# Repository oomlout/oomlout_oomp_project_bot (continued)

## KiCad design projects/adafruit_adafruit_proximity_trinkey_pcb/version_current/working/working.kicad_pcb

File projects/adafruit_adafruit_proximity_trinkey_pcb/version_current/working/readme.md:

# OOMP Project  
## Adafruit-Proximity-Trinkey-PCB  by adafruit  
  
oomp key: oomp_projects_flat_adafruit_adafruit_proximity_trinkey_pcb  
(snippet of original readme)  
  
-- Adafruit Proximity Trinkey PCB  
  
<a href="http://www.adafruit.com/products/5022"><br/>  
Click here to purchase one from the Adafruit shop</a>  
  
PCB files for the Adafruit Proximity Trinkey.   
  
Format is EagleCAD schematic and board layout  
* https://www.adafruit.com/product/5022  
  
--- Description  
  
It's half USB Key, half Adafruit Trinket M0, half APDS9960 breakout...it's Proximity Trinkey, the circuit board with a Trinket M0 heart, APDS9960 Proximity, Light, RGB, and Gesture Sensor, and two RGB NeoPixels for a customizable glow. We wanted to make it super-easy to add one of our most popular combination-sensors to any computer with a USB port and this one is ready to go in an instant.  
  
The PCB is designed to slip into any USB A port on a computer or laptop. There's an ATSAMD21 microcontroller on board with just enough circuitry to keep it happy. One pin of the microcontroller connects to the two NeoPixel LEDs. Two other pins are used as capacitive touch inputs on the end - if you look carefully you can see the slotted end has left and right touch pads. A reset button lets you enter bootloader mode if necessary. That's it!  
  
The SAMD21 can run CircuitPython or Arduino very nicely - both have existing APDS9960, NeoPixel and our FreeTouch (capacitive touch) libraries. Over the USB connection, you can have serial, MIDI, or HID connectivity. The Proximity Trinkey is perfect for simple projects that want to use motion, light or color sen  
  full source readme at [readme_src.md](readme_src.md)  
  
source repo at: [https://github.com/adafruit/Adafruit-Proximity-Trinkey-PCB](https://github.com/adafruit/Adafruit-Proximity-Trinkey-PCB)  
## Board  

## Schematic  

[schematic pdf](working_schematic.pdf)  
## Images

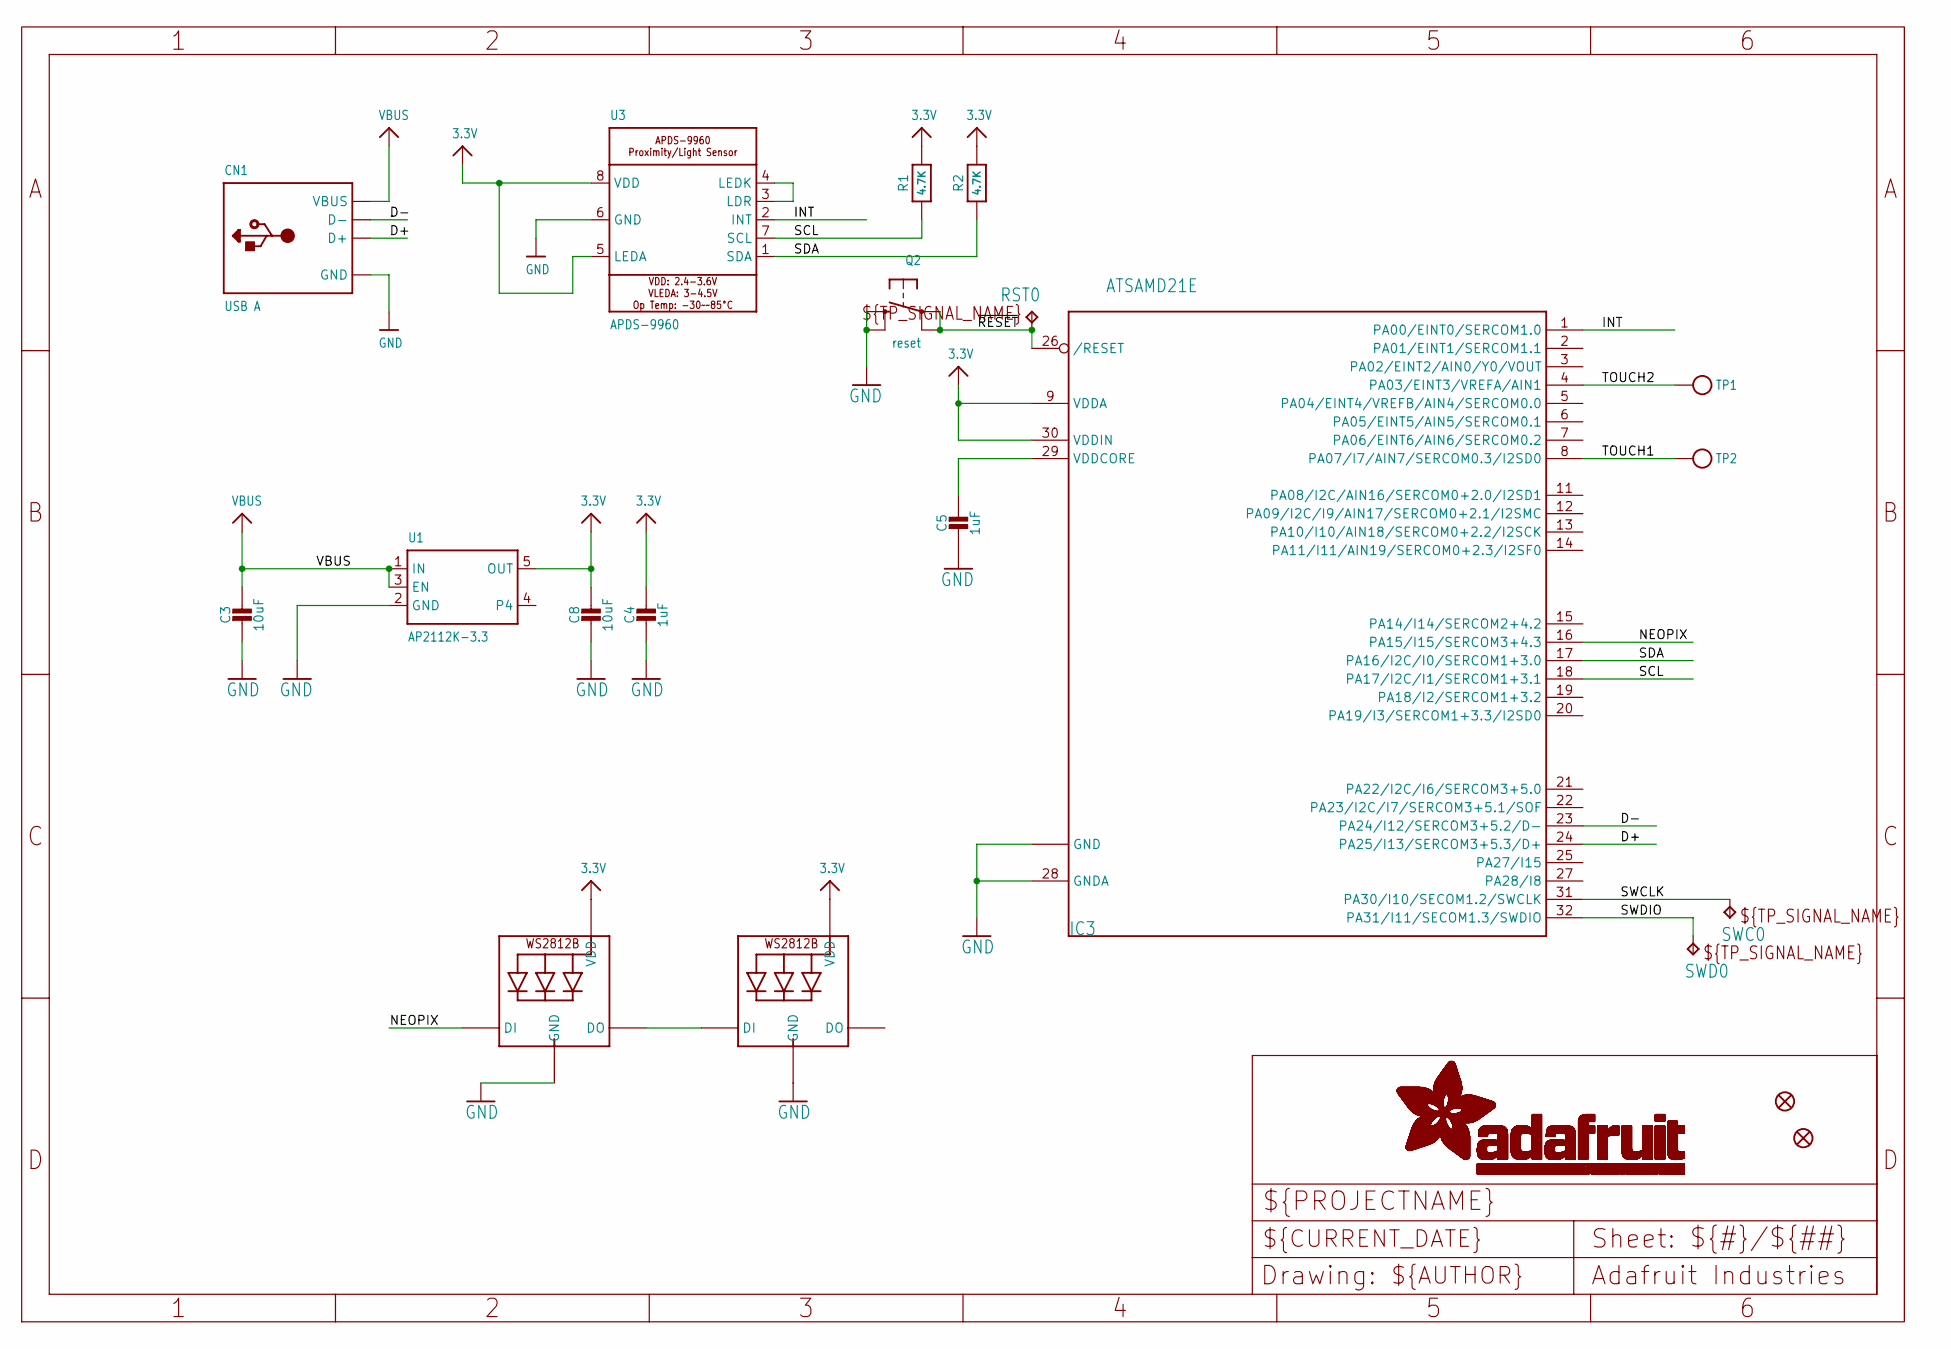
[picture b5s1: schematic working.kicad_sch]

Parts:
C3, C8: 10uF; 0805-NO
C4, C5: 1uF; 0603-NO
CN1: USB A; USBA_PCB
FID1, FID2: FIDUCIAL_1MM
IC3: ATSAMD21E; QFN32_5MM
LED1, LED2: WS2812B3535; LED3535
Q2: reset; BTN_KMR2_4.6X2.8
R1, R2: 4.7K; 0603-NO
RST0: TPTP16R; TP16R
SWC0: TPTP15R; TP15R
SWD0: TPTP16R; TP16R
TP1, TP2: TESTPOINTROUND1.5MMNO; TESTPOINT_ROUND_1.5MM_NO
U1: AP2112K-3.3; SOT23-5
U3: APDS-9960

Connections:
3.3V: C4.1, C8.1, IC3.9 (VDDA), IC3.30 (VDDIN), LED1.2 (VDD), LED2.2 (VDD), R1.2, R2.2, U1.5 (OUT), U3.5 (LEDA), U3.8 (VDD)
D+: CN1.USB_PLUS (D+), IC3.24 (PA25/I13/SERCOM3+5.3/D+)
D-: CN1.USB_NEG (D-), IC3.23 (PA24/I12/SERCOM3+5.2/D-)
GND: C3.2, C4.2, C5.2, C8.2, CN1.GND, IC3.10 (GND), IC3.28 (GNDA), IC3.33 (GND), LED1.4 (GND), LED2.4 (GND), Q2.B (S), Q2.B' (S1), U1.2 (GND), U3.6 (GND)
INT: IC3.1 (PA00/EINT0/SERCOM1.0), U3.2 (INT)
unnamed: LED1.1 (DI), LED2.3 (DO)
unnamed: U3.3 (LDR), U3.4 (LEDK)
NEOPIX: IC3.16 (PA15/I15/SERCOM3+4.3), LED2.1 (DI)
SCL: IC3.18 (PA17/I2C/I1/SERCOM1+3.1), R1.1, U3.7 (SCL)
SDA: IC3.17 (PA16/I2C/I0/SERCOM1+3.0), R2.1, U3.1 (SDA)
SWCLK: IC3.31 (PA30/I10/SECOM1.2/SWCLK), SWC0.TP
SWDIO: IC3.32 (PA31/I11/SECOM1.3/SWDIO), SWD0.TP
TOUCH1: IC3.8 (PA07/I7/AIN7/SERCOM0.3/I2SD0), TP2.P$1
TOUCH2: IC3.4 (PA03/EINT3/VREFA/AIN1), TP1.P$1
VBUS: C3.1, CN1.VCC (VBUS), U1.1 (IN), U1.3 (EN)
VDDCORE1: C5.1, IC3.29 (VDDCORE)
~RESET: IC3.26 (/RESET), Q2.A, Q2.A' (P1), RST0.TP

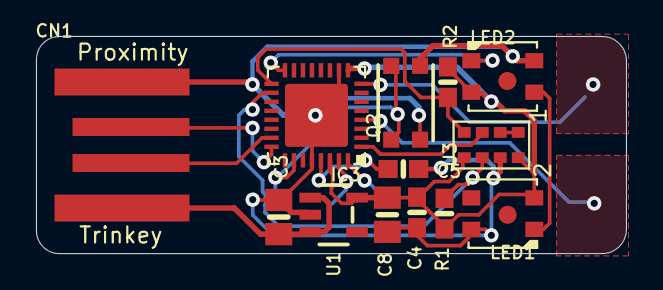
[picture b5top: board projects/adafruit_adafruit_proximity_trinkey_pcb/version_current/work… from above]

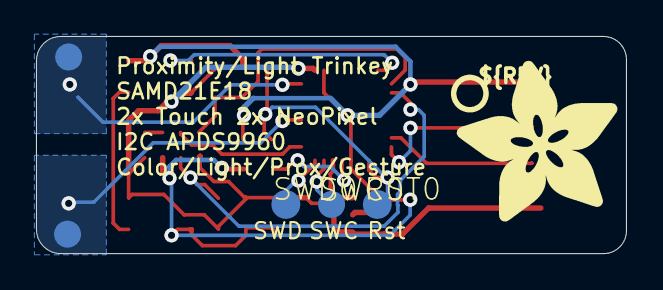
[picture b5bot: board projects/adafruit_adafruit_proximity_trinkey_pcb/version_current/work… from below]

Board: 2 copper layers, 32.8 x 12.1 mm, 22 parts (7 on the bottom side), 17 nets.

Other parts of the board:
U$8: PCBFEAT-REV-040
U$10: ADAFRUIT_9MM

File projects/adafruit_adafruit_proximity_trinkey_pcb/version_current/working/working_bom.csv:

Row,Description,Part,References,Value,Footprint,Quantity Per PCB,Status,Datasheet
1,,CAP_CERAMIC0603_NO,C4 C5,1uF,0603-NO,2, ,
2,,CAP_CERAMIC0805-NOOUTLINE,C3 C8,10uF,0805-NO,2, ,
3,,USB_TYPEAPCB,CN1,USB A,USBA_PCB,1, ,
4,,ATSAMD21E,IC3,ATSAMD21E,QFN32_5MM,1, ,
5,,WS2812B3535,LED1 LED2,WS2812B3535,LED3535,2, ,
6,,SWITCH_TACT_SMT4.6X2.8,Q2,reset,BTN_KMR2_4.6X2.8,1, ,
7,,RESISTOR_0603_NOOUT,R1 R2,4.7K,0603-NO,2, ,
8,,TPTP16R,RST0 SWD0,TPTP16R,TP16R,2, ,
9,,TPTP15R,SWC0,TPTP15R,TP15R,1, ,
10,,VREG_SOT23-5,U1,AP2112K-3.3,SOT23-5,1, ,
11,,APDS-9960,U3,APDS-9960,APDS-9960,1, ,





Project info:
Schematic:,working
Variant:,default
Revision:,
Date:,2023-08-03_17-21-23
KiCad Version:,7.0.6-7.0.6~ubuntu22.04.1
Statistics:
Component Groups:,11
Component Count:,16 (0 SMD/ 0 THT)
Fitted Components:,16 (0 SMD/ 0 THT)
Number of PCBs:,1
Total Components:,16

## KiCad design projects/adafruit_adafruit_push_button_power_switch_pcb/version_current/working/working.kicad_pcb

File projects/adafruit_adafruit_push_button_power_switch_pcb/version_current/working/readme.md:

# OOMP Project  
## Adafruit-Push-Button-Power-Switch-PCB  by adafruit  
  
oomp key: oomp_projects_flat_adafruit_adafruit_push_button_power_switch_pcb  
(snippet of original readme)  
  
-- Adafruit Push Button Power Switch PCB  
<a href="http://www.adafruit.com/products/1400"><br/>  
Click here to purchase one from the Adafruit shop</a>  
  
The Adafruit Push-button Power Switch is a tidy little design that lets you control a DC power source using an everyday tactile button. The breakout uses a latching analog circuit that is triggered by a push of the button. Press once to turn on, then press again to turn off. The circuit uses a 3A P-FET to connect and disconnect the IN pin to the OUT pin. Works great from 3V to 14VDC and up to 3A (although the FET gets a little toasty at continuous 3A draw) yet has only 0.5uA quiescent current draw.  
  
Using it is easy: connect the power source to Ground and IN, then the load from Ground to OUT. We include a 12mm tactile switch that works well but you can solder in your own switch as well. Press the button (or short the button pins) to alternate between on or off. A on-board red LED will light up when active so you know its working. There's a fourth KILL pin, which you can use to turn off the load and/or keep it off even if the button is pressed. When 1 or more volts is applied it will instantly turn off the FET. This allows your project to turn itself off.  
  
Comes with a assembled & tested bread-board friendly breakout board with four mounting holes, a 12mm tactile button, and some 0.1" male header you can solder to the board to plug it into a breadboard.  
  
PCB files for the Push Bu  
  full source readme at [readme_src.md](readme_src.md)  
  
source repo at: [https://github.com/adafruit/Adafruit-Push-Button-Power-Switch-PCB](https://github.com/adafruit/Adafruit-Push-Button-Power-Switch-PCB)  
## Board  

## Schematic  

[schematic pdf](working_schematic.pdf)  
## Images

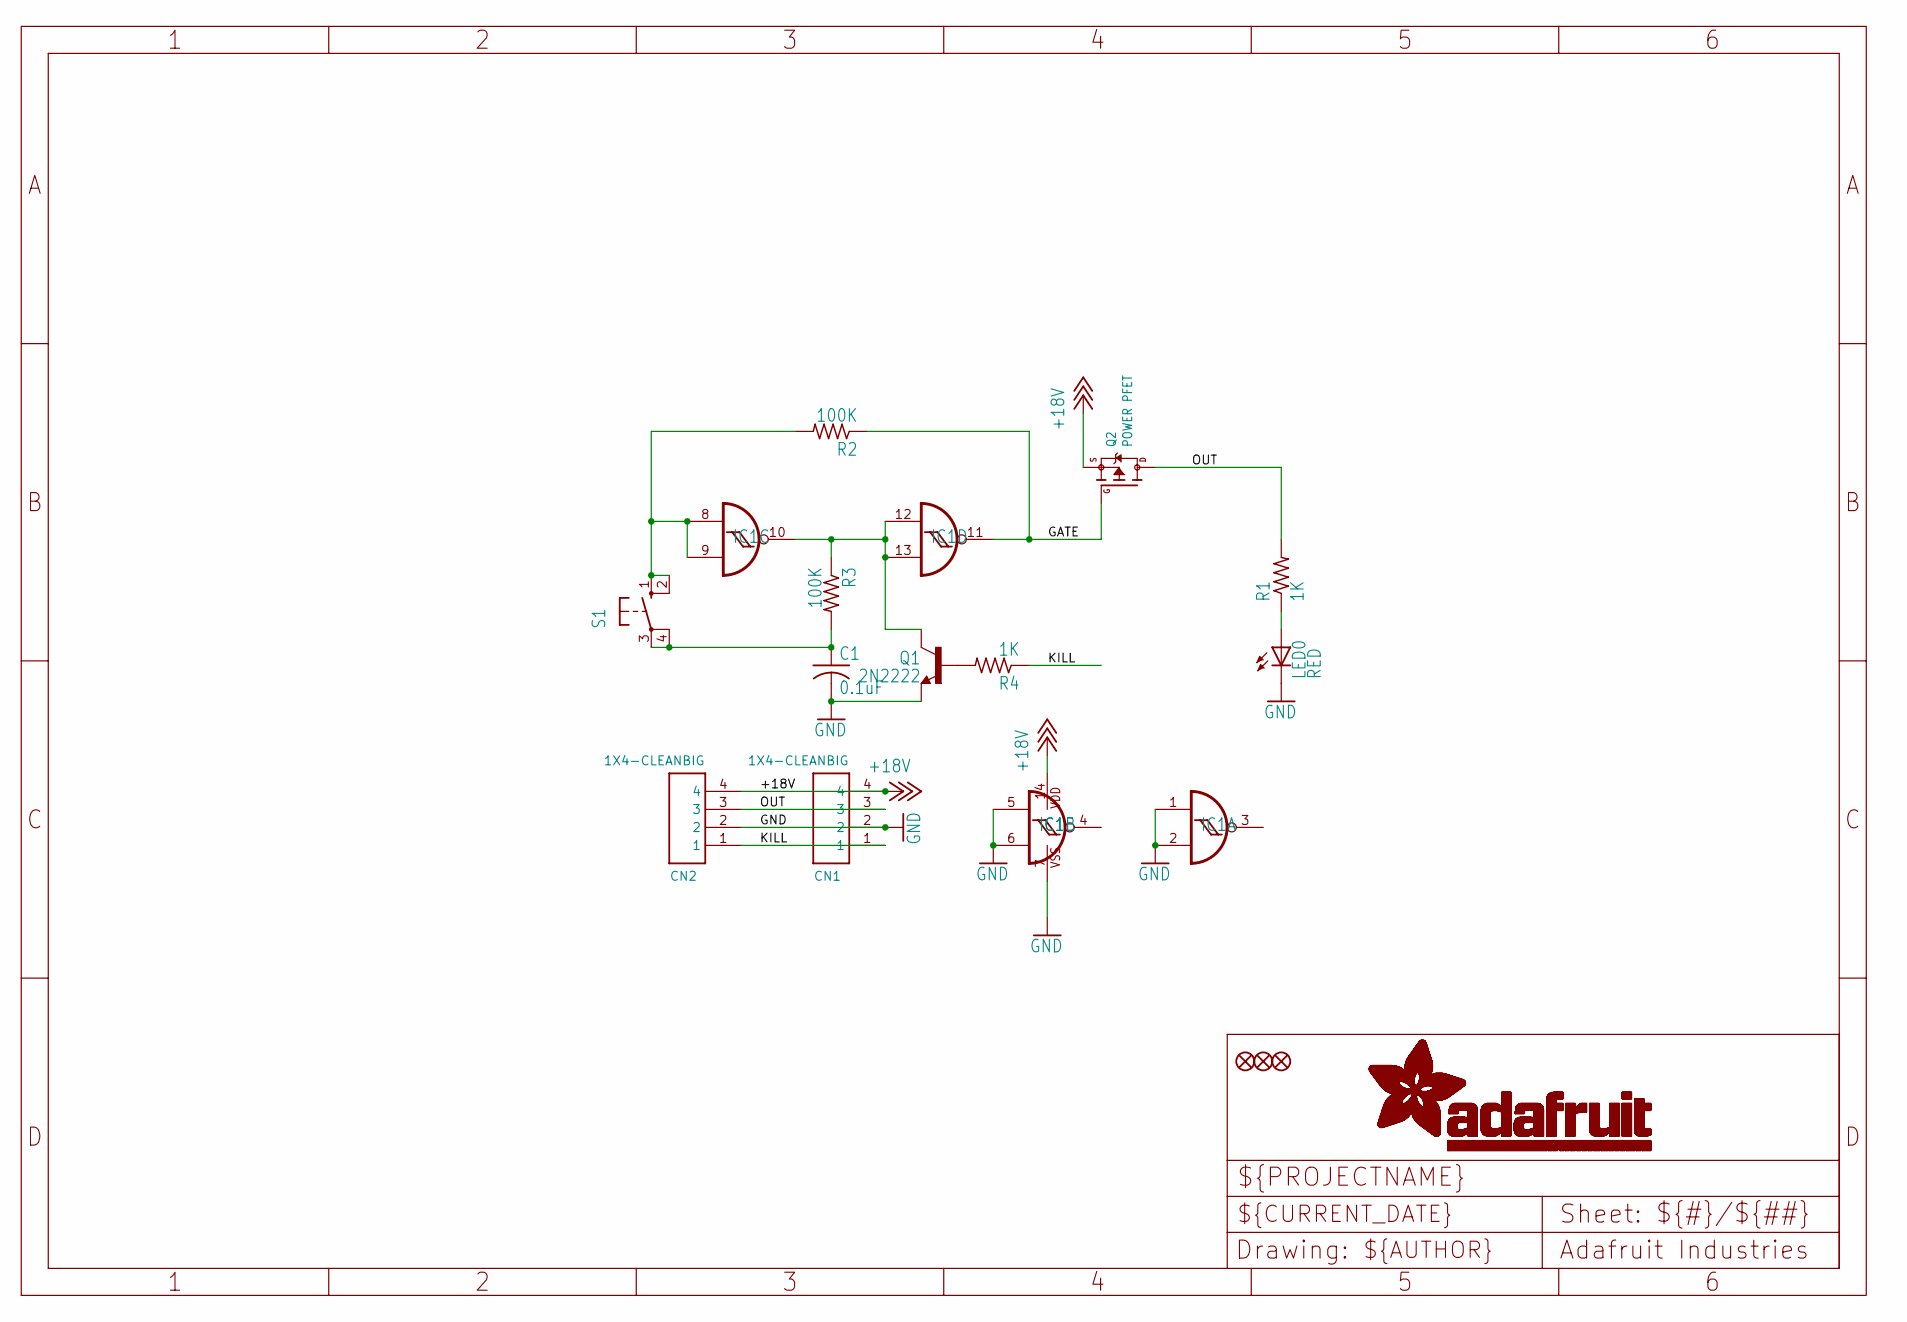
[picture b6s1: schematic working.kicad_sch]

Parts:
C1: 0.1uF; C0805
CN1, CN2: 1X4-CLEANBIG; 1X04-CLEANBIG
FID1, FID2, FID3: FIDUCIAL""; FIDUCIAL_1MM
IC1: 4093DT; MC14093B-TSSOP14
LED0: RED; CHIP-LED0805
Q1: 2N2222; SOT23-BEC
Q2: POWER PFET; SOT23-WIDE
R1, R4: 1K; R0805
R2, R3: 100K; R0805
S1: 40-XX-ROUND; B3F-40XX-ROUND

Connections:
+18V: CN1.4, CN2.4, IC1.14 (VDD), Q2.2 (S)
GATE: IC1.11 (O), Q2.1 (G), R2.1
GND: C1.2, CN1.2, CN2.2, IC1.1 (I0), IC1.2 (I1), IC1.5 (I0), IC1.6 (I1), IC1.7 (VSS), LED0.C, Q1.E
KILL: CN1.1, CN2.1, R4.1
unnamed: Q1.B, R4.2
unnamed: IC1.10 (O), IC1.12 (I0), IC1.13 (I1), Q1.C, R3.1
unnamed: LED0.A, R1.1
unnamed: C1.1, R3.2, S1.3, S1.4 (P1)
unnamed: IC1.8 (I0), IC1.9 (I1), R2.2, S1.1 (S), S1.2 (S1)
OUT: CN1.3, CN2.3, Q2.3 (D), R1.2

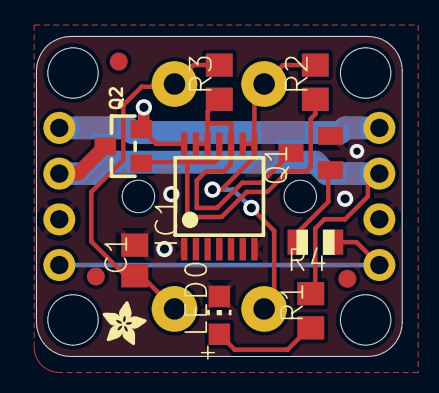
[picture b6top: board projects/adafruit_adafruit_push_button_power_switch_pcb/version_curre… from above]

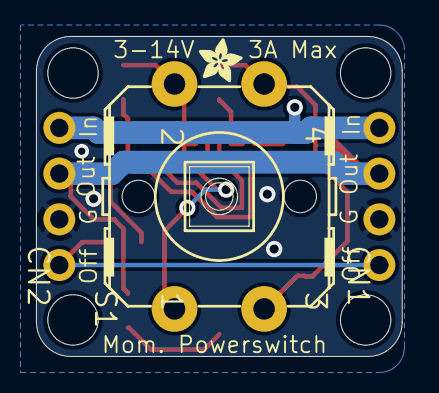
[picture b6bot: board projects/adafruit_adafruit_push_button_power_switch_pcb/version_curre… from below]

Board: 2 copper layers, 20.3 x 17.8 mm, 21 parts (4 on the bottom side), 10 nets.

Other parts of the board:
@HOLE0, @HOLE1, @HOLE2, @HOLE3: (no value)
U$1, U$2: ADAFRUIT_2.5MM

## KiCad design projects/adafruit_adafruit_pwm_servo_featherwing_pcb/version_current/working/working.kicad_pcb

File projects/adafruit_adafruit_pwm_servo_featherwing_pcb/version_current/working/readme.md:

# Adafruit-PWM-Servo-FeatherWing-PCB by adafruit  
This is a harvested standardized copy of a project from github.  
The original project can be found at:  
https://github.com/adafruit/Adafruit-PWM-Servo-FeatherWing-PCB  
Please consult that link for additional, details, files, and license information.  
Note: It was auto harvested and if the original repo had more than one board file or anything out of the ordinary the files here are likely not representative.

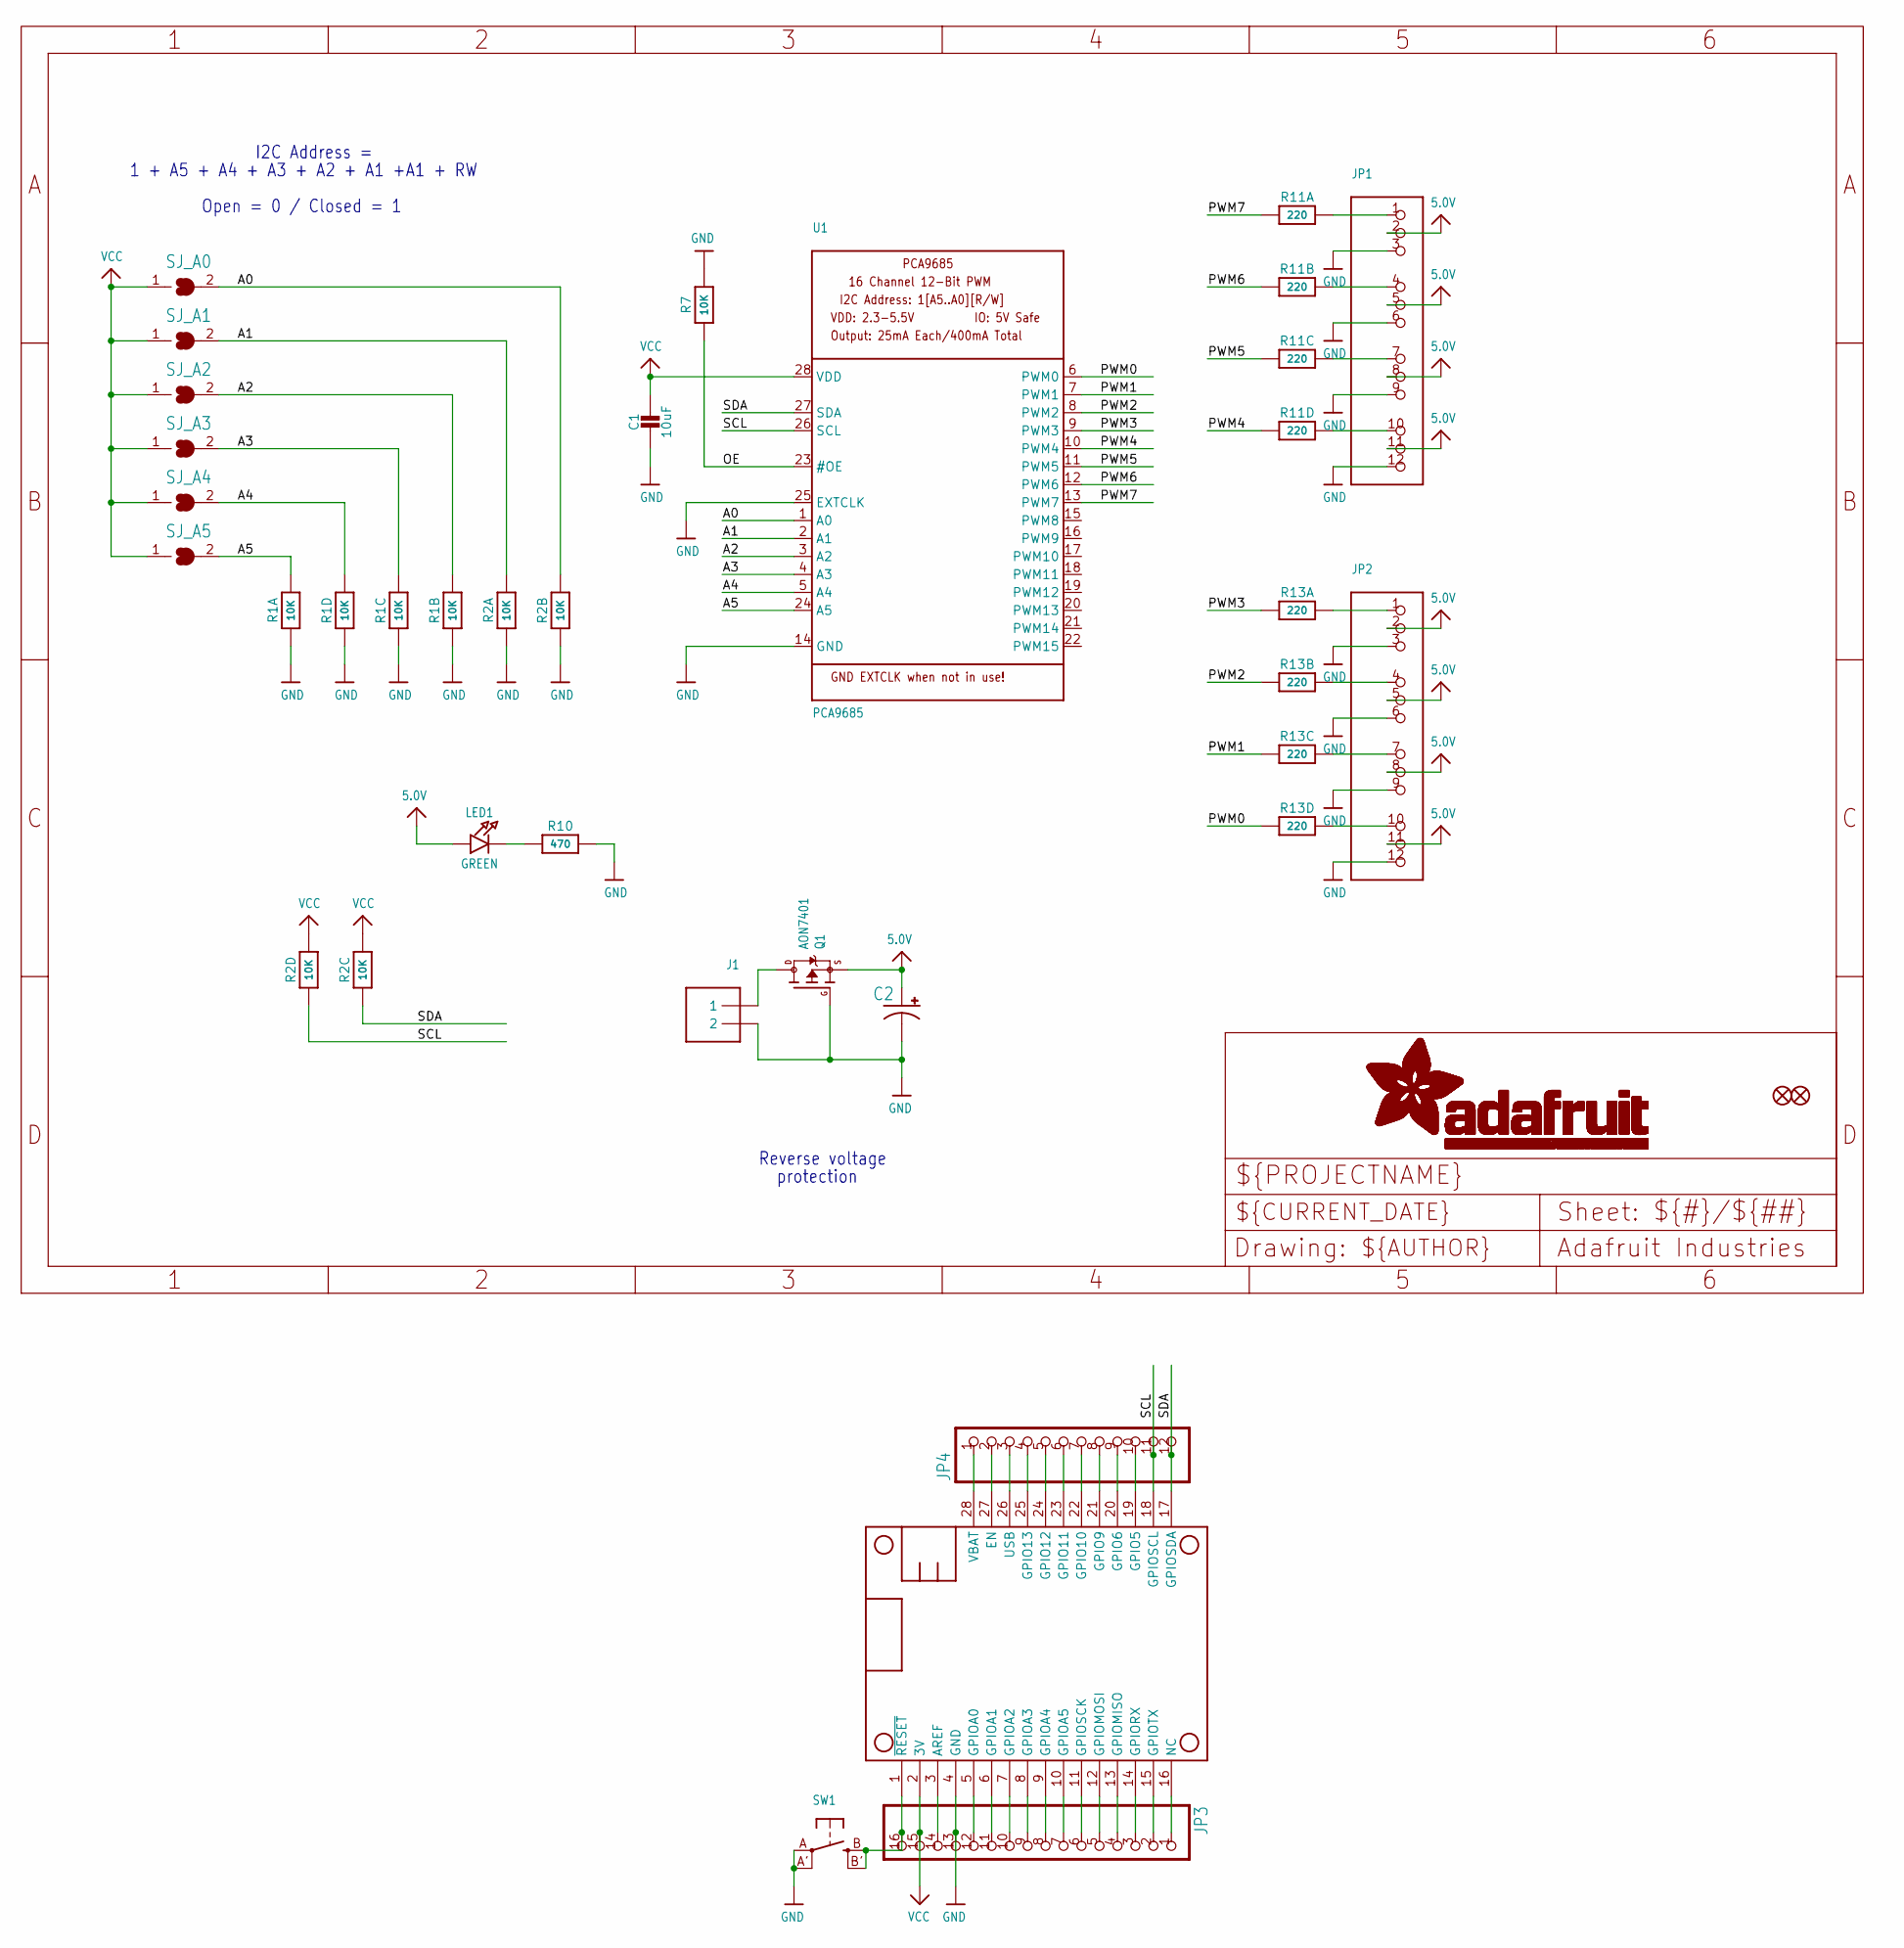
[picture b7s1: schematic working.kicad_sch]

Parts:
C1: 10uF; 0805-NO
C2: CPOL-USE3.5-8; E3,5-8
FID1, FID2: FIDUCIAL""; FIDUCIAL_1MM
J1: TERMBLOCK_1X2; TERMBLOCK_1X2-3.5MM
JP1, JP2: HEADER-3X04; 3X04
JP3: HEADER-1X16ROUND; 1X16_ROUND
JP4: HEADER-1X12; 1X12_ROUND
LED1: GREEN; CHIPLED_0805_NOOUTLINE
MS1: FEATHERWING
Q1: AON7401; POWERDI3333
R1, R2: 10K; RESPACK_4X0603
R7: 10K; 0805-NO
R10: 470; 0805-NO
R11, R13: 220; RESPACK_4X0603
SJ_A0, SJ_A1, SJ_A2, SJ_A3, SJ_A4, SJ_A5: SOLDERJUMPERREFLOW_NOPASTE; SOLDERJUMPER_REFLOW_NOPASTE
SW1: SWITCH_TACT_SMT4.6X2.8; BTN_KMR2_4.6X2.8
U1: PCA9685; TSSOP28

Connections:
5.0V: C2.+, JP1.2, JP1.5, JP1.8, JP1.11, JP2.2, JP2.5, JP2.8, JP2.11, LED1.A, Q1.1 (S), Q1.2 (S), Q1.3 (S)
A0: R2.7 (2), SJ_A0.2, U1.1 (A0)
A1: R2.8 (2), SJ_A1.2, U1.2 (A1)
A2: R1.7 (2), SJ_A2.2, U1.3 (A2)
A3: R1.6 (2), SJ_A3.2, U1.4 (A3)
A4: R1.5 (2), SJ_A4.2, U1.5 (A4)
A5: R1.8 (2), SJ_A5.2, U1.24 (A5)
GND: C1.2, C2.-, J1.2, JP1.3, JP1.6, JP1.9, JP1.12, JP2.3, JP2.6, JP2.9, JP2.12, JP3.13, MS1.4 (GND), Q1.4 (G), R1.1, R1.2 (1), R1.3 (1), R1.4 (1), R2.1, R2.2 (1), R7.2, R10.2, SW1.A, SW1.A' (P1), U1.14 (GND), U1.25 (EXTCLK)
unnamed: LED1.C, R10.1
unnamed: JP1.4, R11.7 (2)
unnamed: JP1.1, R11.8 (2)
unnamed: JP1.7, R11.6 (2)
unnamed: JP1.10, R11.5 (2)
unnamed: JP2.1, R13.8 (2)
unnamed: JP2.4, R13.7 (2)
unnamed: JP2.7, R13.6 (2)
unnamed: JP2.10, R13.5 (2)
unnamed: JP3.1, MS1.16 (NC)
unnamed: JP3.2, MS1.15 (GPIOTX)
unnamed: JP3.3, MS1.14 (GPIORX)
unnamed: JP3.4, MS1.13 (GPIOMISO)
unnamed: JP3.5, MS1.12 (GPIOMOSI)
unnamed: JP3.6, MS1.11 (GPIOSCK)
unnamed: JP3.7, MS1.10 (GPIOA5)
unnamed: JP3.8, MS1.9 (GPIOA4)
unnamed: JP3.9, MS1.8 (GPIOA3)
unnamed: JP3.10, MS1.7 (GPIOA2)
unnamed: JP3.11, MS1.6 (GPIOA1)
unnamed: JP3.12, MS1.5 (GPIOA0)
unnamed: JP3.14, MS1.3 (AREF)
unnamed: JP4.2, MS1.27 (EN)
unnamed: JP4.4, MS1.25 (GPIO13)
unnamed: JP4.5, MS1.24 (GPIO12)
unnamed: JP4.6, MS1.23 (GPIO11)
unnamed: JP4.7, MS1.22 (GPIO10)
unnamed: JP4.8, MS1.21 (GPIO9)
unnamed: JP4.9, MS1.20 (GPIO6)
unnamed: JP4.10, MS1.19 (GPIO5)
unnamed: JP3.16, MS1.1 (~RESET), SW1.B (S), SW1.B' (S1)
OE: R7.1, U1.23 (#OE)
PWM0: R13.4 (1), U1.6 (PWM0)
PWM1: R13.3 (1), U1.7 (PWM1)
PWM2: R13.2 (1), U1.8 (PWM2)
PWM3: R13.1, U1.9 (PWM3)
PWM4: R11.4 (1), U1.10 (PWM4)
PWM5: R11.3 (1), U1.11 (PWM5)
PWM6: R11.2 (1), U1.12 (PWM6)
PWM7: R11.1, U1.13 (PWM7)
PWRIN: J1.1, Q1.5678 (D)
SCL: JP4.11, MS1.18 (GPIOSCL), R2.4 (1), U1.26 (SCL)
SDA: JP4.12, MS1.17 (GPIOSDA), R2.3 (1), U1.27 (SDA)
USB: JP4.3, MS1.26 (USB)
VBAT: JP4.1, MS1.28 (VBAT)
VCC: C1.1, JP3.15, MS1.2 (3V), R2.5 (2), R2.6 (2), SJ_A0.1, SJ_A1.1, SJ_A2.1, SJ_A3.1, SJ_A4.1, SJ_A5.1, U1.28 (VDD)

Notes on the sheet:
I2C Address =
1 + A5 + A4 + A3 + A2 + A1 +A1 + RW
Reverse voltage
Open = 0 / Closed = 1
protection

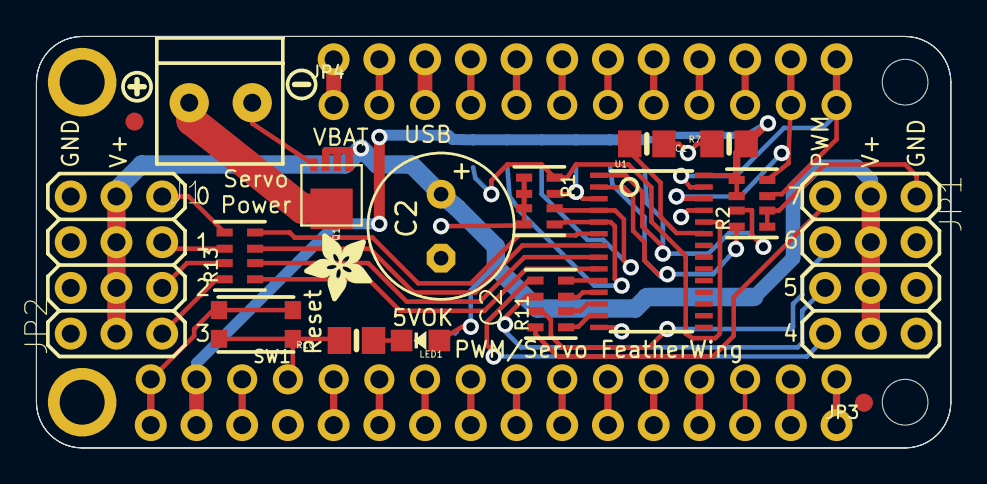
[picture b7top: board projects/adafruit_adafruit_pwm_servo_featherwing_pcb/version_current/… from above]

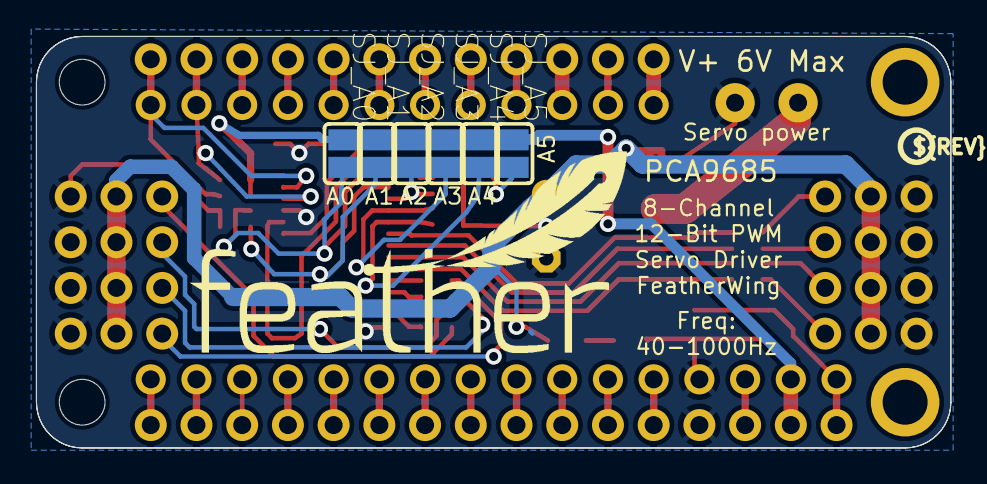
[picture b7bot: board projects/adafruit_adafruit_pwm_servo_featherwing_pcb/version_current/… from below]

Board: 2 copper layers, 50.8 x 22.9 mm, 31 parts (8 on the bottom side), 54 nets.

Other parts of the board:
U$11: SYMBOL_PLUS
U$12: SYMBOL_MINUS
U$14: ADAFRUIT_3.5MM
U$15: FEATHERLOGO
U$16: PCBFEAT-REV-040
